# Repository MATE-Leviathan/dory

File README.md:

# Dory

A custom control and power distribution board for NCSSM Morganton Robotics.

## Why this exists

This board started as a wiring problem.

On the robot, too many things were being connected with loose jumper wires, splitters, adapters, and one-off harnesses. It worked, but it was annoying to build, annoying to trace, and even more annoying to debug when something came loose. Every extra wire was another failure point, and every repair meant spending time figuring out which connection had moved instead of working on the robot.

Float PCB is meant to clean that up. It brings the common controller, power, sensor, light, and debug connections onto one board so the robot is easier to assemble, easier to service, and less dependent on fragile wiring.

## Board evolution

The design went through several revisions while the board moved from a simple rectangular breakout toward the current round layout with cleaner connector placement, clearer labels, and more intentional branding.

## Features

- **ESP32-S3 controller** using an ESP32-S3-WROOM-1U module for onboard control and wireless-capable development.
- **External antenna support** through the ESP32-S3-WROOM-1U module for more flexible radio placement.
- **USB-C interface** for programming, debugging, and convenient bench access.
- **XT30 battery input** for a more robust main power connector than loose leads.
- **64 mm round board outline** for a compact layout that fits cleanly into the robot.
- **4-layer PCB stackup** with front/back signal layers and two internal power layers.
- **5V and 3.3V regulation** using TPSM863252 power modules.
- **ESP-controlled 5V enable** so software can turn the 5V rail on or off when needed.
- **Onboard buzzer** for audible alerts, even when the board is mounted inside the robot.
- **External light output** for driving a Blue Robotics-style indicator or robot status light.
- **Dual I2C ports** on JST-XH connectors for cleaner sensor wiring.
- **Robot I/O connectors** for switch, light, servo, buzzer, and miscellaneous expansion signals.
- **Battery sensing** through a resistor divider and dedicated `BATT_ADC` test point.
- **Status LEDs** for battery, 5V, and 3.3V rails.
- **USB ESD protection** on the USB data lines.
- **Debug/test access** with labeled test points for power rails, boot, enable, I2C, and ground.
- **Mechanical mounting** with three M2 mounting holes.

## Hardware overview

The board is built around an ESP32-S3-WROOM-1U module and breaks out the useful robot-facing signals to keyed or serviceable connectors. The PCB is a 64 mm diameter, 4-layer circular board with front and back signal routing plus two internal power layers. Power enters through an XT30 connector, then the onboard regulators generate the rails needed by the controller and peripherals.

The intent is not to replace every subsystem on the robot. The goal is to provide a cleaner central board for the connections that otherwise turn into messy wiring: power, I2C devices, lights, switches, a buzzer, servo control, battery monitoring, and spare expansion lines.

## Work in progress

The current plan is to use the onboard ESP32 as the robot-side controller and pair it with a separate ESP32-based base station. The base station will communicate with the ESP32 on the Float PCB, giving the robot a cleaner wireless control/debug path without needing to plug directly into the board every time.

An accompanying web interface is also planned. The site will be built with Svelte and use Web Serial so a laptop can talk to the ESP32 base station directly from the browser. The goal is to make setup, monitoring, and debugging accessible without requiring a custom desktop app.

## Repository contents

- `float_pcb.kicad_pro` — KiCad project file.
- `float_pcb.kicad_sch` — schematic source.
- `float_pcb.kicad_pcb` — PCB layout source.
- `jlcpcb/production_files/` — generated BOM, CPL, and Gerber ZIP for JLCPCB.
- `jlcpcb/gerber/` — expanded Gerber and drill outputs.
- `float_pcb.csv` — project BOM/export data.
- `digikey/order.csv` — DigiKey ordering file.
- `images/` — README and board/team branding assets.

## Manufacturing

The repository includes production outputs under `jlcpcb/production_files/`:

- `GERBER-float_pcb.zip`
- `BOM-float_pcb.csv`
- `CPL-float_pcb.csv`

Before ordering, re-open the project in KiCad, refill zones, run DRC/ERC, and regenerate production files from the latest schematic and PCB layout. The checked-in files are useful for handoff, but the KiCad sources should be treated as the source of truth.

For component ordering, use `digikey/order.csv` as the DigiKey order file.

## Known issues

- One of the I2C ports is about 0.025 mm off in the Z direction. This is only for people with OCD like me; it should not matter for normal assembly.
- The fancy QFN buck converter packages are hard to solder by hand. If you want to build this board, make sure you have solder paste, reflow, and patience, or redesign that power stage around something friendlier like a SOT-23 package.

## Development notes

- Designed in KiCad.
- Uses mostly SMD passives with JST-XH, XT30, USB-C, and pin-header connections.
- Includes test points for bring-up and debugging.
- Intended for robotics use where reliability and serviceability matter more than minimizing every connector or square millimeter.

## Team

Built for NCSSM Morganton Robotics as a practical fix for too much robot wiring.

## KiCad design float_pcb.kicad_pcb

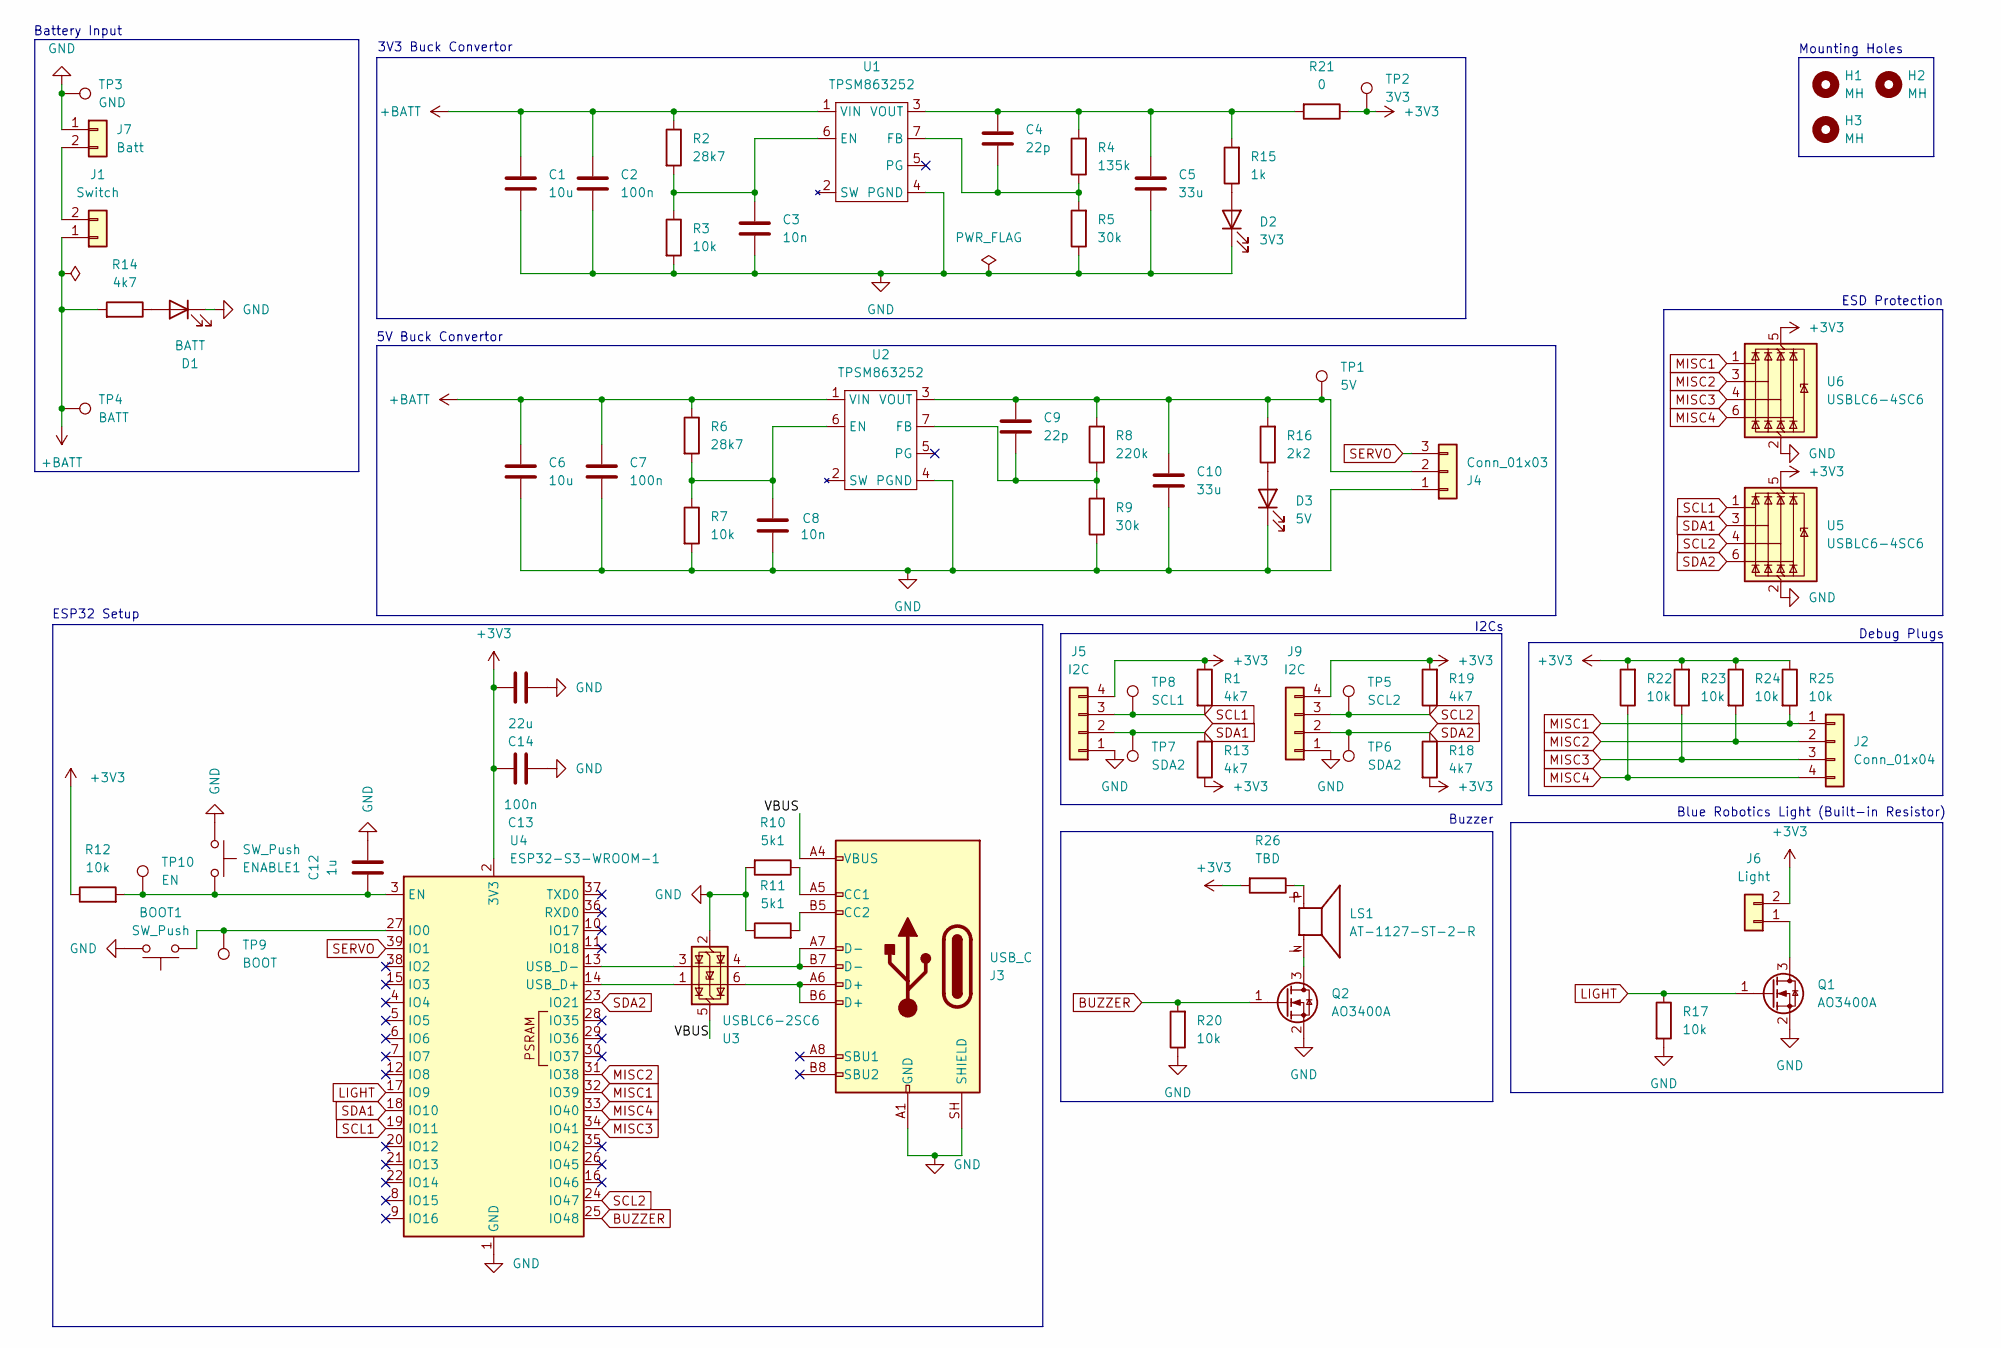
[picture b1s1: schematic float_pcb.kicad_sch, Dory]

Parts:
BOOT1: SW_Push; SW_SPST_TL3342
C1, C6: 10u; C_0805_2012Metric
C2, C7, C13: 100n; C_0603_1608Metric
C3, C8: 10n; C_0603_1608Metric
C4, C9: 22p; C_0603_1608Metric
C5, C10: 33u; C_0805_2012Metric
C12: 1u; C_0603_1608Metric
C14: 22u; C_0603_1608Metric
D1: BATT; LED_0603_1608Metric
D2: 3V3; LED_0603_1608Metric
D3: 5V; LED_0603_1608Metric
ENABLE1: SW_Push; SW_SPST_TL3342
H1, H2, H3: MH; MountingHole_2.2mm_M2
J1: Switch; JST_XH_B2B-XH-A_1x02_P2.50mm_Vertical
J2: Conn_01x04; PinHeader_1x04_P2.54mm_Vertical
J3: USB_C; USB_C_Receptacle_GCT_USB4105-xx-A_16P_TopMnt_Horizontal
J4: Conn_01x03; JST_XH_B3B-XH-A_1x03_P2.50mm_Vertical
J5, J9: I2C; JST_XH_B4B-XH-A_1x04_P2.50mm_Vertical
J6: Light; JST_XH_B2B-XH-A_1x02_P2.50mm_Vertical
J7: Batt; AMASS_XT30U-M_1x02_P5.0mm_Vertical
LS1: AT-1127-ST-2-R; XDCR_AT-1127-ST-2-R; PARTREV C
Q1, Q2: AO3400A; SOT-23
R1, R13, R14, R18, R19: 4k7; R_0603_1608Metric
R2, R6: 28k7; R_0603_1608Metric
R3, R7, R12, R17, R20, R22, R23, R24, R25: 10k; R_0603_1608Metric
R4: 135k; R_0603_1608Metric
R5, R9: 30k; R_0603_1608Metric
R8: 220k; R_0603_1608Metric
R10, R11: 5k1; R_0603_1608Metric
R15: 1k; R_0603_1608Metric
R16: 2k2; R_0603_1608Metric
R21: 0; R_0603_1608Metric
R26: TBD; R_0603_1608Metric
TP1: 5V; TestPoint_Pad_D1.5mm
TP2: 3V3; TestPoint_Pad_D1.5mm
TP3: GND; TestPoint_Pad_D1.5mm
TP4: BATT; TestPoint_Pad_D1.5mm
TP5: SCL2; TestPoint_Pad_D1.5mm
TP6, TP7: SDA2; TestPoint_Pad_D1.5mm
TP8: SCL1; TestPoint_Pad_D1.5mm
TP9: BOOT; TestPoint_Pad_D1.5mm
TP10: EN; TestPoint_Pad_D1.5mm
U1, U2: TPSM863252; TPSM86325x_RDX0007A
U3: USBLC6-2SC6; SOT-23-6
U4: ESP32-S3-WROOM-1; ESP32-S3-WROOM-1U
U5, U6: USBLC6-4SC6; SOT-23-6

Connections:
+3V3: C13.1, C14.1, J5.4, J6.2, J9.4, R1.1, R12.1, R13.1, R18.2, R19.2, R21.1, R22.2, R23.2, R24.1, R25.1, R26.2, TP2.1 (1_1), U4.2 (3V3), U5.5 (VBUS), U6.5 (VBUS)
+BATT: C1.1, C2.2, C6.1, C7.2, J1.1, R2.1, R6.1, R14.2, TP4.1 (1_1), U1.1 (VIN), U2.1 (VIN)
/VBUS: J3.A4 (VBUS), J3.A9 (VBUS), J3.B4 (VBUS), J3.B9 (VBUS), U3.5 (VBUS)
BUZZER: Q2.1 (G), R20.2, U4.25 (IO48)
GND: BOOT1.2, C1.2, C2.1, C3.1, C5.1, C6.2, C7.1, C8.2, C10.1, C12.1, C13.2, C14.2, D1.1 (K), D2.1 (K), D3.1 (K), ENABLE1.1, J3.A1 (GND), J3.A12 (GND), J3.B1 (GND), J3.B12 (GND), J3.SH (SHIELD), J4.1, J5.1, J7.1, J9.1, Q1.2 (S), Q2.2 (S), R3.2, R5.1, R7.2, R9.1, R10.2, R11.1, R17.2, R20.1, TP3.1 (1_1), U1.4 (PGND), U2.4 (PGND), U3.2 (GND), U4.1 (GND), U4.40 (GND), U4.41 (GND), U5.2 (GND), U6.2 (GND)
LIGHT: Q1.1 (G), R17.1, U4.17 (IO9)
MISC1: J2.1, R25.2, U4.32 (IO39), U6.1 (I/O1)
MISC2: J2.2, R24.2, U4.31 (IO38), U6.3 (I/O2)
MISC3: J2.3, R23.1, U4.34 (IO41), U6.4 (I/O3)
MISC4: J2.4, R22.1, U4.33 (IO40), U6.6 (I/O4)
unnamed: D1.2 (A), R14.1
unnamed: D2.2 (A), R15.1
unnamed: D3.2 (A), R16.1
unnamed: J1.2, J7.2
unnamed: J3.A5 (CC1), R10.1
unnamed: J3.B5 (CC2), R11.2
unnamed: J3.A6 (D+), J3.B6 (D+), U3.6 (I/O1)
unnamed: J3.A7 (D-), J3.B7 (D-), U3.4 (I/O2)
unnamed: C9.1, C10.2, J4.2, R8.2, R16.2, TP1.1 (1_1), U2.3 (VOUT)
unnamed: J6.1, Q1.3 (D)
unnamed: LS1.P, R26.1
unnamed: LS1.N, Q2.3 (D)
unnamed: C3.2, R2.2, R3.1, U1.6 (EN)
unnamed: C4.2, R4.1, R5.2, U1.7 (FB)
unnamed: C4.1, C5.2, R4.2, R15.2, R21.2, U1.3 (VOUT)
unnamed: C8.1, R6.2, R7.1, U2.6 (EN)
unnamed: C9.2, R8.1, R9.2, U2.7 (FB)
unnamed: C12.2, ENABLE1.2, R12.2, TP10.1 (1_1), U4.3 (EN)
unnamed: BOOT1.1, TP9.1 (1_1), U4.27 (IO0)
unnamed: U3.1 (I/O1), U4.14 (USB_D+)
unnamed: U3.3 (I/O2), U4.13 (USB_D-)
SCL1: J5.3, R1.2, TP8.1 (1_1), U4.19 (IO11), U5.1 (I/O1)
SCL2: J9.3, R19.1, TP5.1 (1_1), U4.24 (IO47), U5.4 (I/O3)
SDA1: J5.2, R13.2, TP7.1 (1_1), U4.18 (IO10), U5.3 (I/O2)
SDA2: J9.2, R18.1, TP6.1 (1_1), U4.23 (IO21), U5.6 (I/O4)
SERVO: J4.3, U4.39 (IO1)

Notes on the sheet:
Mounting Holes
ESP32 Setup
I2Cs
ESD Protection
Battery Input
3V3 Buck Convertor
Blue Robotics Light (Built-in Resistor)
5V Buck Convertor
Buzzer
Debug Plugs

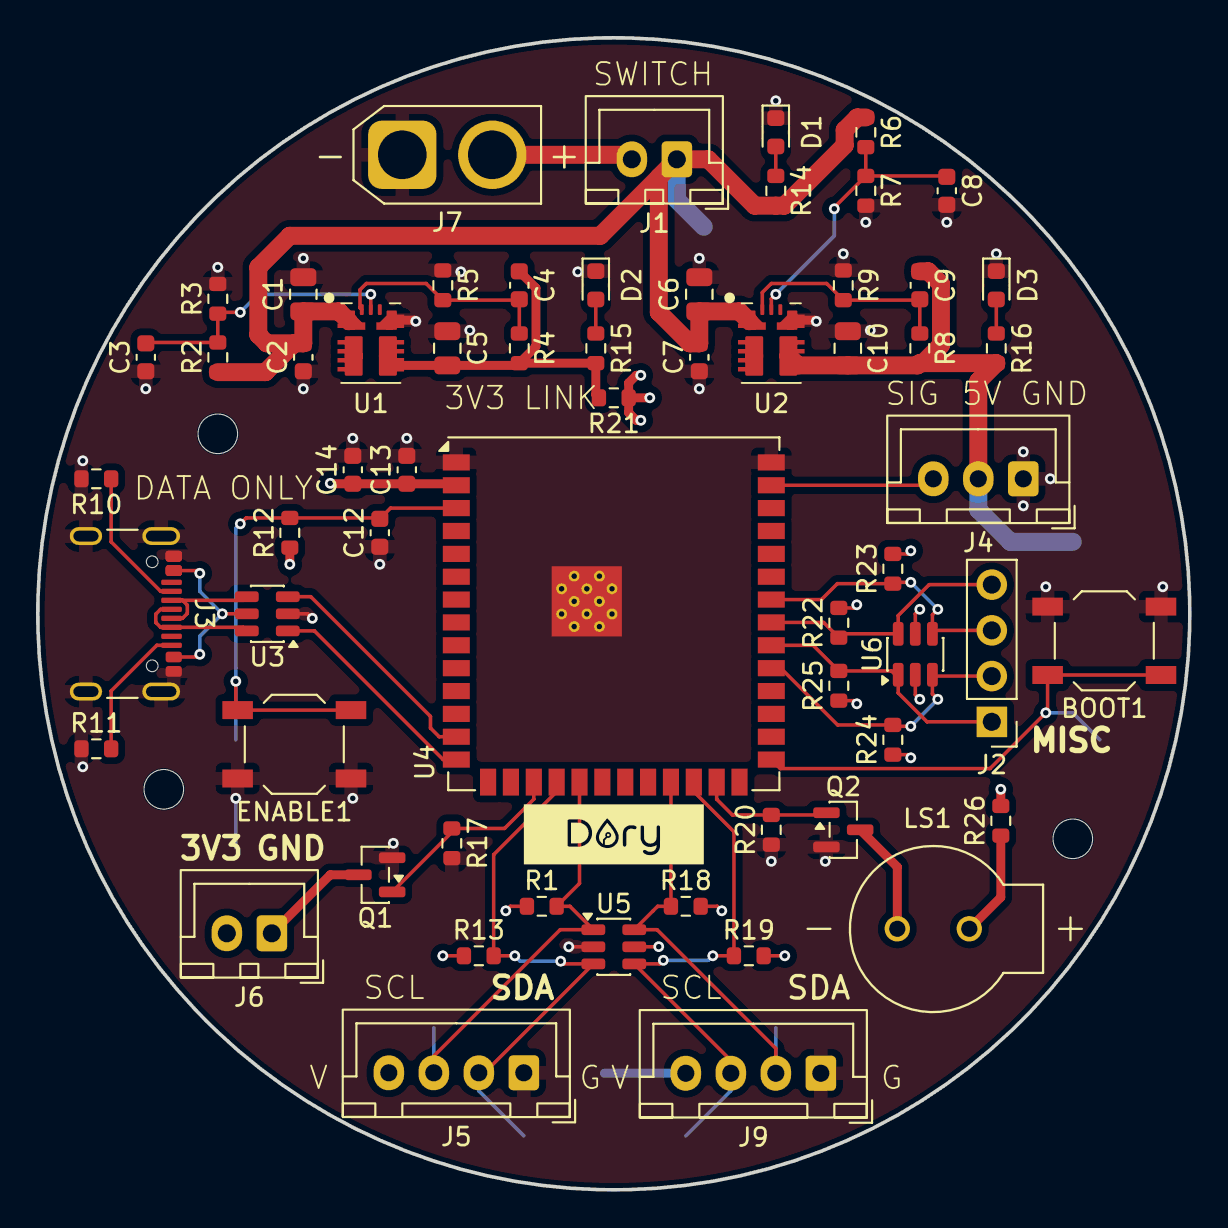
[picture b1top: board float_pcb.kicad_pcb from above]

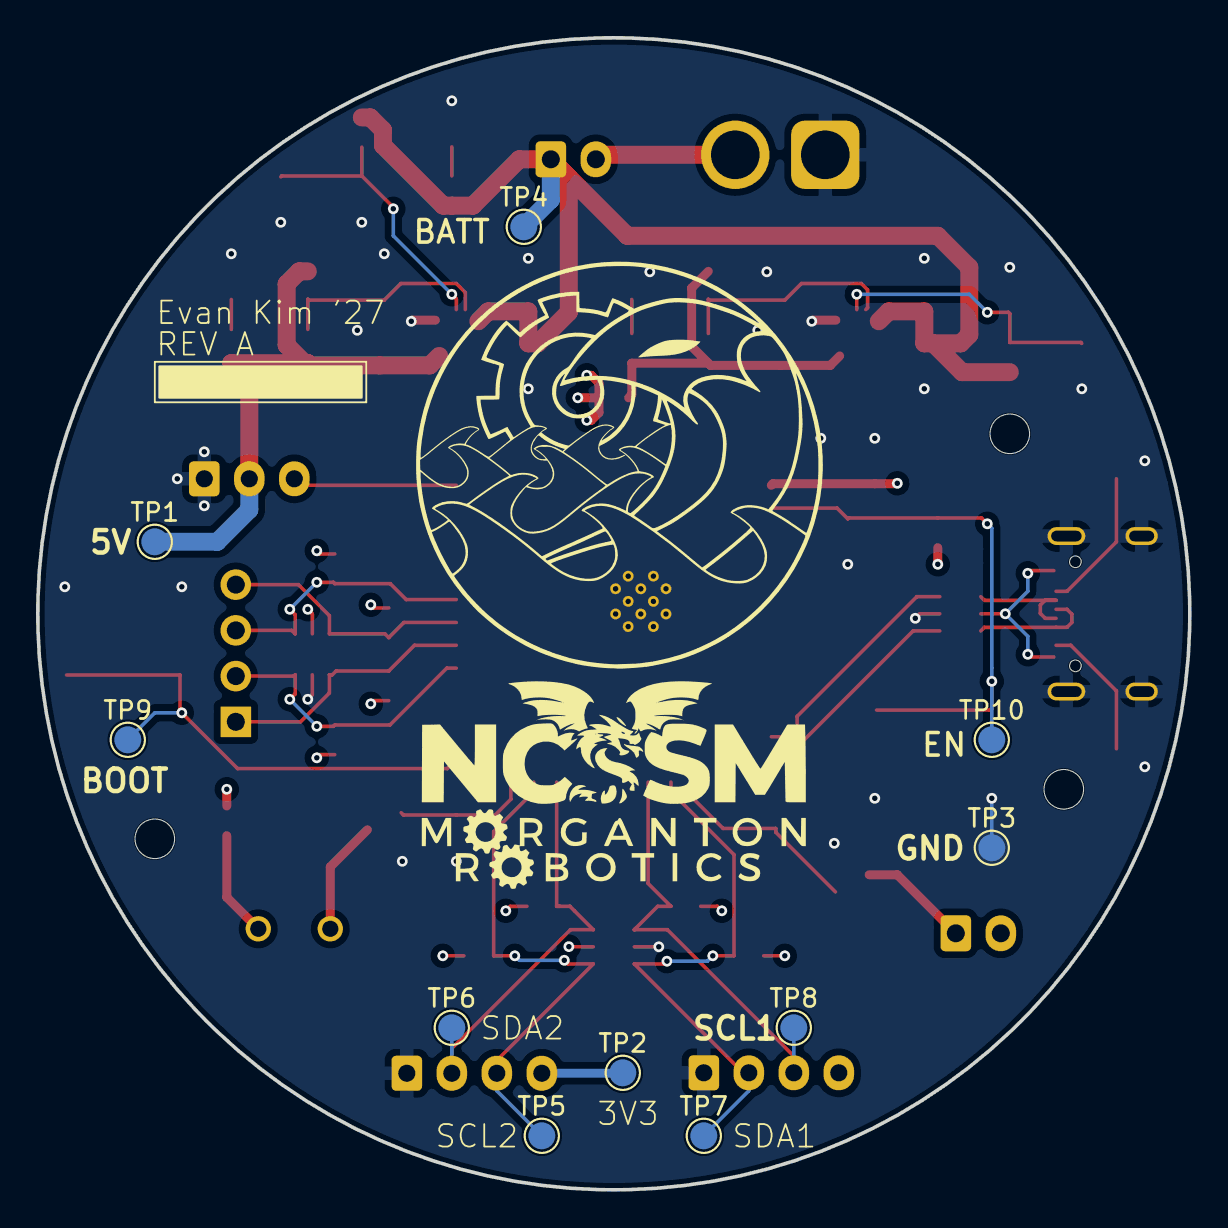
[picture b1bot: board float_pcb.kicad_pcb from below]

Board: 4 copper layers, 64.0 x 64.0 mm, 74 parts (10 on the bottom side), 36 nets.

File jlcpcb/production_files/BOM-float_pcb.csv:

Comment,Designator,Footprint,LCSC,Quantity
Light,J6,JST_XH_B2B-XH-A_1x02_P2.50mm_Vertical,,1
Switch,J1,JST_XH_B2B-XH-A_1x02_P2.50mm_Vertical,,1
22u,C14,C_0603_1608Metric,,1
100n,C7,C_0603_1608Metric,,1
28k7,R6,R_0603_1608Metric,,1
AO3400A,Q1,SOT-23,,1
22p,C4,C_0603_1608Metric,,1
5V,D3,LED_0603_1608Metric,,1
2k2,R16,R_0603_1608Metric,,1
100n,C2,C_0603_1608Metric,,1
5k1,R11,R_0603_1608Metric,,1
10n,C3,C_0603_1608Metric,,1
10k,R7,R_0603_1608Metric,,1
33u,C5,C_0805_2012Metric,,1
TPSM863252,U2,TPSM86325x_RDX0007A,,1
100n,C13,C_0603_1608Metric,,1
1u,C12,C_0603_1608Metric,,1
10k,R3,R_0603_1608Metric,,1
220k,R8,R_0603_1608Metric,,1
SW_Push,BOOT1,SW_SPST_TL3342,,1
10u,C6,C_0805_2012Metric,,1
10k,R12,R_0603_1608Metric,,1
4k7,R13,R_0603_1608Metric,,1
28k7,R2,R_0603_1608Metric,,1
Batt,J7,AMASS_XT30U-M_1x02_P5.0mm_Vertical,,1
33u,C10,C_0805_2012Metric,,1
4k7,R14,R_0603_1608Metric,,1
135k,R4,R_0603_1608Metric,,1
10u,C1,C_0805_2012Metric,,1
4k7,R1,R_0603_1608Metric,,1
USB_C,J3,USB_C_Receptacle_GCT_USB4105-xx-A_16P_TopMnt_Horizontal,,1
30k,R9,R_0603_1608Metric,,1
1k,R15,R_0603_1608Metric,,1
3V3,D2,LED_0603_1608Metric,,1
TPSM863252,U1,TPSM86325x_RDX0007A,,1
10n,C8,C_0603_1608Metric,,1
I2C,J5,JST_XH_B4B-XH-A_1x04_P2.50mm_Vertical,,1
5k1,R10,R_0603_1608Metric,,1
30k,R5,R_0603_1608Metric,,1
22p,C9,C_0603_1608Metric,,1
BATT,D1,LED_0603_1608Metric,,1
SW_Push,ENABLE1,SW_SPST_TL3342,,1
10k,R17,R_0603_1608Metric,,1
4k7,R19,R_0603_1608Metric,,1
4k7,R18,R_0603_1608Metric,,1
I2C,J9,JST_XH_B4B-XH-A_1x04_P2.50mm_Vertical,,1
10k,R20,R_0603_1608Metric,,1
AO3400A,Q2,SOT-23,,1
AT-1127-ST-2-R,LS1,XDCR_AT-1127-ST-2-R,,1
Conn_01x03,J4,JST_XH_B3B-XH-A_1x03_P2.50mm_Vertical,,1
ESP32-S3-WROOM-1,U4,ESP32-S3-WROOM-1U,,1
Conn_01x04,J2,PinHeader_1x04_P2.54mm_Vertical,,1
BATT,TP4,TestPoint_Pad_D1.5mm,,1
GND,TP3,TestPoint_Pad_D1.5mm,,1
3V3,TP2,TestPoint_Pad_D1.5mm,,1
5V,TP1,TestPoint_Pad_D1.5mm,,1
USBLC6-2SC6,U3,SOT-23-6,,1
USBLC6-4SC6,U5,SOT-23-6,,1
USBLC6-4SC6,U6,SOT-23-6,,1
TBD,R26,R_0603_1608Metric,,1
10k,R25,R_0603_1608Metric,,1
10k,R24,R_0603_1608Metric,,1
10k,R23,R_0603_1608Metric,,1
10k,R22,R_0603_1608Metric,,1
0,R21,R_0603_1608Metric,,1
EN,TP10,TestPoint_Pad_D1.5mm,,1
SDA2,TP6,TestPoint_Pad_D1.5mm,,1
BOOT,TP9,TestPoint_Pad_D1.5mm,,1
SCL2,TP5,TestPoint_Pad_D1.5mm,,1
SDA2,TP7,TestPoint_Pad_D1.5mm,,1
SCL1,TP8,TestPoint_Pad_D1.5mm,,1

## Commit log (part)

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2026-05-18 Add some things
2026-05-18 more changes
2026-06-02 Progress
2026-06-02 Almost done with V4
2026-06-06 Added a README
2026-06-06 Add project title
